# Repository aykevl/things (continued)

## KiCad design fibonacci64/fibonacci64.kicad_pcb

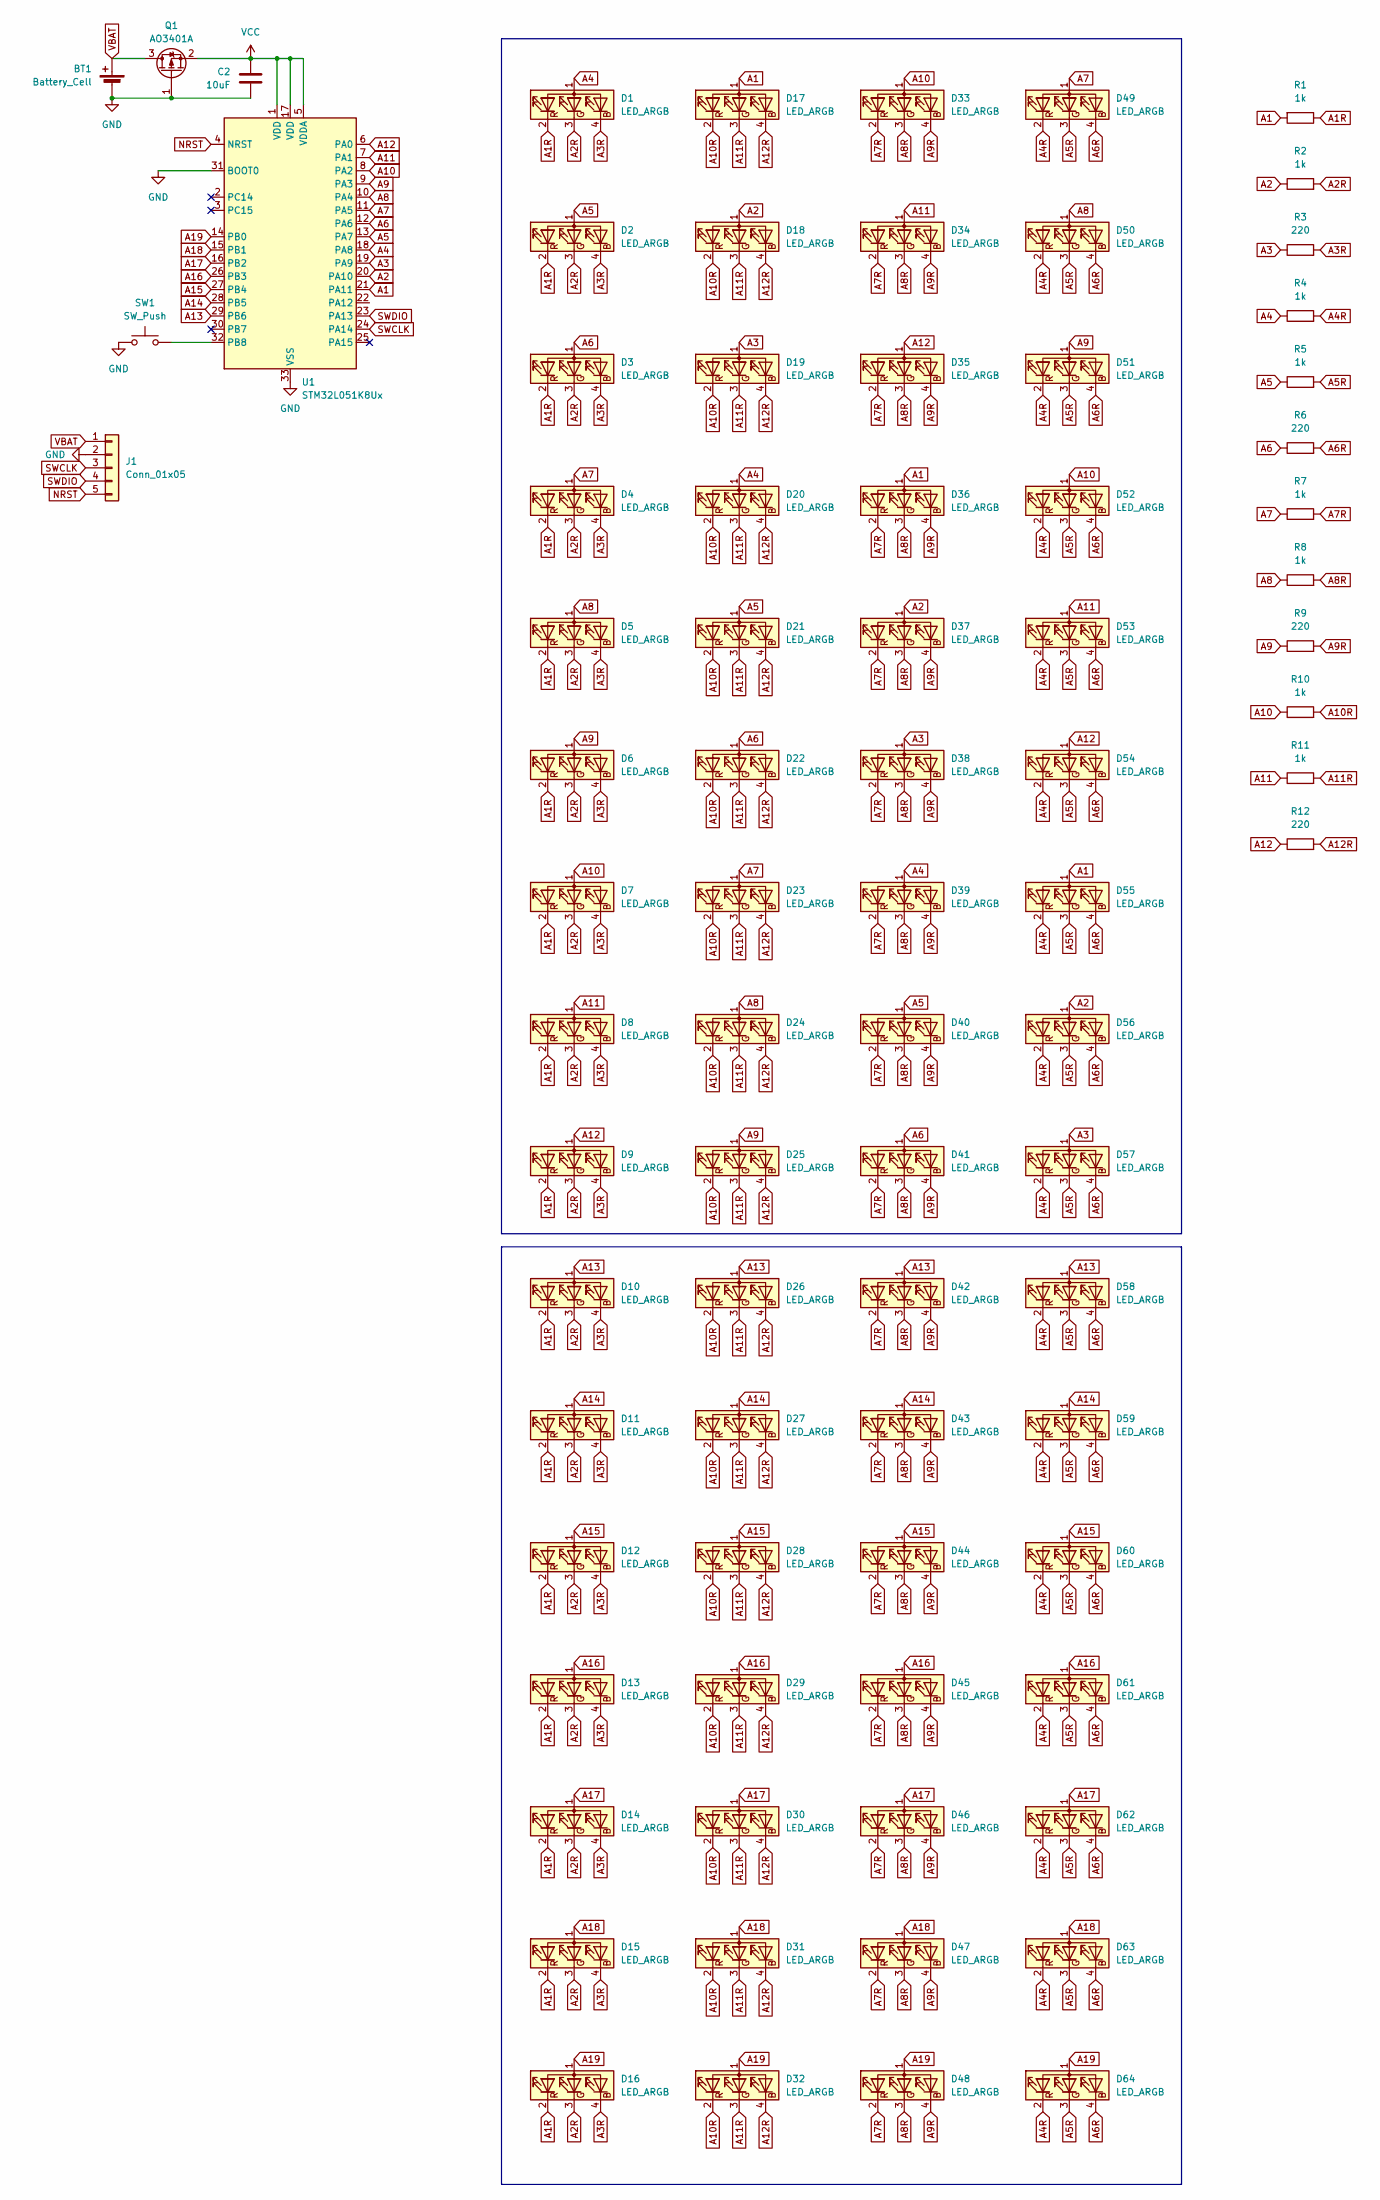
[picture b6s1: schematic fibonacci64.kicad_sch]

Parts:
BT1: Battery_Cell; BatteryHolder_Keystone_1060_1x2032; LCSC C964818
C2: 10uF; C_0402_1005Metric; LCSC C15525
D1, D2, D3, D4, D5, D6, D7, D8, D9, D10, D11, D12, D13, D14, D15, D16, D17, D18, D19, D20, D21, D22, D23, D24, D25, D26, D27, D28, D29, D30, D31, D32, D33, D34, D35, D36, D37, D38, D39, D40, D41, D42, D43, D44, D45, D46, D47, D48, D49, D50, D51, D52, D53, D54, D55, D56, D57, D58, D59, D60, D61, D62, D63, D64: LED_ARGB; NH-Z1415RGBA-SG; LCSC C2874117
J1: Conn_01x05; ProgramHeader
Q1: AO3401A; SOT-23; LCSC C15127
R1, R2, R4, R5, R7, R8, R10, R11: 1k; R_0402_1005Metric; LCSC C11702
R3, R6, R9, R12: 220; R_0402_1005Metric; LCSC C25091
SW1: SW_Push; SW_Push_SPST_NO_Alps_SKRK; LCSC C720477
U1: STM32L051K8Ux; QFN-32-1EP_5x5mm_P0.5mm_EP3.45x3.45mm; LCSC C94770

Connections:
A1: D17.1 (A), D36.1 (A), D55.1 (A), R1.2, U1.21 (PA11)
A1R: D1.2 (RK), D2.2 (RK), D3.2 (RK), D4.2 (RK), D5.2 (RK), D6.2 (RK), D7.2 (RK), D8.2 (RK), D9.2 (RK), D10.2 (RK), D11.2 (RK), D12.2 (RK), D13.2 (RK), D14.2 (RK), D15.2 (RK), D16.2 (RK), R1.1
A2: D18.1 (A), D37.1 (A), D56.1 (A), R2.1, U1.20 (PA10)
A2R: D1.3 (GK), D2.3 (GK), D3.3 (GK), D4.3 (GK), D5.3 (GK), D6.3 (GK), D7.3 (GK), D8.3 (GK), D9.3 (GK), D10.3 (GK), D11.3 (GK), D12.3 (GK), D13.3 (GK), D14.3 (GK), D15.3 (GK), D16.3 (GK), R2.2
A3: D19.1 (A), D38.1 (A), D57.1 (A), R3.1, U1.19 (PA9)
A3R: D1.4 (BK), D2.4 (BK), D3.4 (BK), D4.4 (BK), D5.4 (BK), D6.4 (BK), D7.4 (BK), D8.4 (BK), D9.4 (BK), D10.4 (BK), D11.4 (BK), D12.4 (BK), D13.4 (BK), D14.4 (BK), D15.4 (BK), D16.4 (BK), R3.2
A4: D1.1 (A), D20.1 (A), D39.1 (A), R4.1, U1.18 (PA8)
A4R: D49.2 (RK), D50.2 (RK), D51.2 (RK), D52.2 (RK), D53.2 (RK), D54.2 (RK), D55.2 (RK), D56.2 (RK), D57.2 (RK), D58.2 (RK), D59.2 (RK), D60.2 (RK), D61.2 (RK), D62.2 (RK), D63.2 (RK), D64.2 (RK), R4.2
A5: D2.1 (A), D21.1 (A), D40.1 (A), R5.1, U1.13 (PA7)
A5R: D49.3 (GK), D50.3 (GK), D51.3 (GK), D52.3 (GK), D53.3 (GK), D54.3 (GK), D55.3 (GK), D56.3 (GK), D57.3 (GK), D58.3 (GK), D59.3 (GK), D60.3 (GK), D61.3 (GK), D62.3 (GK), D63.3 (GK), D64.3 (GK), R5.2
A6: D3.1 (A), D22.1 (A), D41.1 (A), R6.1, U1.12 (PA6)
A6R: D49.4 (BK), D50.4 (BK), D51.4 (BK), D52.4 (BK), D53.4 (BK), D54.4 (BK), D55.4 (BK), D56.4 (BK), D57.4 (BK), D58.4 (BK), D59.4 (BK), D60.4 (BK), D61.4 (BK), D62.4 (BK), D63.4 (BK), D64.4 (BK), R6.2
A7: D4.1 (A), D23.1 (A), D49.1 (A), R7.1, U1.11 (PA5)
A7R: D33.2 (RK), D34.2 (RK), D35.2 (RK), D36.2 (RK), D37.2 (RK), D38.2 (RK), D39.2 (RK), D40.2 (RK), D41.2 (RK), D42.2 (RK), D43.2 (RK), D44.2 (RK), D45.2 (RK), D46.2 (RK), D47.2 (RK), D48.2 (RK), R7.2
A8: D5.1 (A), D24.1 (A), D50.1 (A), R8.1, U1.10 (PA4)
A8R: D33.3 (GK), D34.3 (GK), D35.3 (GK), D36.3 (GK), D37.3 (GK), D38.3 (GK), D39.3 (GK), D40.3 (GK), D41.3 (GK), D42.3 (GK), D43.3 (GK), D44.3 (GK), D45.3 (GK), D46.3 (GK), D47.3 (GK), D48.3 (GK), R8.2
A9: D6.1 (A), D25.1 (A), D51.1 (A), R9.1, U1.9 (PA3)
A9R: D33.4 (BK), D34.4 (BK), D35.4 (BK), D36.4 (BK), D37.4 (BK), D38.4 (BK), D39.4 (BK), D40.4 (BK), D41.4 (BK), D42.4 (BK), D43.4 (BK), D44.4 (BK), D45.4 (BK), D46.4 (BK), D47.4 (BK), D48.4 (BK), R9.2
A10: D7.1 (A), D33.1 (A), D52.1 (A), R10.1, U1.8 (PA2)
A10R: D17.2 (RK), D18.2 (RK), D19.2 (RK), D20.2 (RK), D21.2 (RK), D22.2 (RK), D23.2 (RK), D24.2 (RK), D25.2 (RK), D26.2 (RK), D27.2 (RK), D28.2 (RK), D29.2 (RK), D30.2 (RK), D31.2 (RK), D32.2 (RK), R10.2
A11: D8.1 (A), D34.1 (A), D53.1 (A), R11.1, U1.7 (PA1)
A11R: D17.3 (GK), D18.3 (GK), D19.3 (GK), D20.3 (GK), D21.3 (GK), D22.3 (GK), D23.3 (GK), D24.3 (GK), D25.3 (GK), D26.3 (GK), D27.3 (GK), D28.3 (GK), D29.3 (GK), D30.3 (GK), D31.3 (GK), D32.3 (GK), R11.2
A12: D9.1 (A), D35.1 (A), D54.1 (A), R12.1, U1.6 (PA0)
A12R: D17.4 (BK), D18.4 (BK), D19.4 (BK), D20.4 (BK), D21.4 (BK), D22.4 (BK), D23.4 (BK), D24.4 (BK), D25.4 (BK), D26.4 (BK), D27.4 (BK), D28.4 (BK), D29.4 (BK), D30.4 (BK), D31.4 (BK), D32.4 (BK), R12.2
A13: D10.1 (A), D26.1 (A), D42.1 (A), D58.1 (A), U1.29 (PB6)
A14: D11.1 (A), D27.1 (A), D43.1 (A), D59.1 (A), U1.28 (PB5)
A15: D12.1 (A), D28.1 (A), D44.1 (A), D60.1 (A), U1.27 (PB4)
A16: D13.1 (A), D29.1 (A), D45.1 (A), D61.1 (A), U1.26 (PB3)
A17: D14.1 (A), D30.1 (A), D46.1 (A), D62.1 (A), U1.16 (PB2)
A18: D15.1 (A), D31.1 (A), D47.1 (A), D63.1 (A), U1.15 (PB1)
A19: D16.1 (A), D32.1 (A), D48.1 (A), D64.1 (A), U1.14 (PB0)
GND: BT1.2 (-), C2.2, J1.2, Q1.1 (G), SW1.2, U1.31 (BOOT0), U1.33 (VSS)
NRST: J1.5, U1.4 (NRST)
unnamed: SW1.1, U1.32 (PB8)
SWCLK: J1.3, U1.24 (PA14)
SWDIO: J1.4, U1.23 (PA13)
VBAT: BT1.1 (+), J1.1, Q1.3 (D)
VCC: C2.1, Q1.2 (S), U1.1 (VDD), U1.5 (VDDA), U1.17 (VDD)

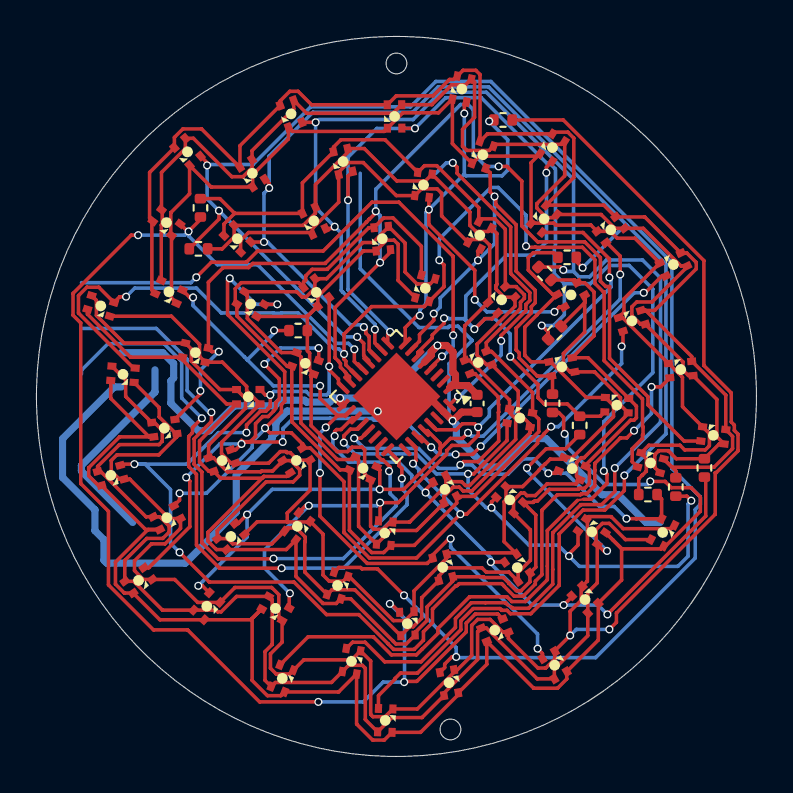
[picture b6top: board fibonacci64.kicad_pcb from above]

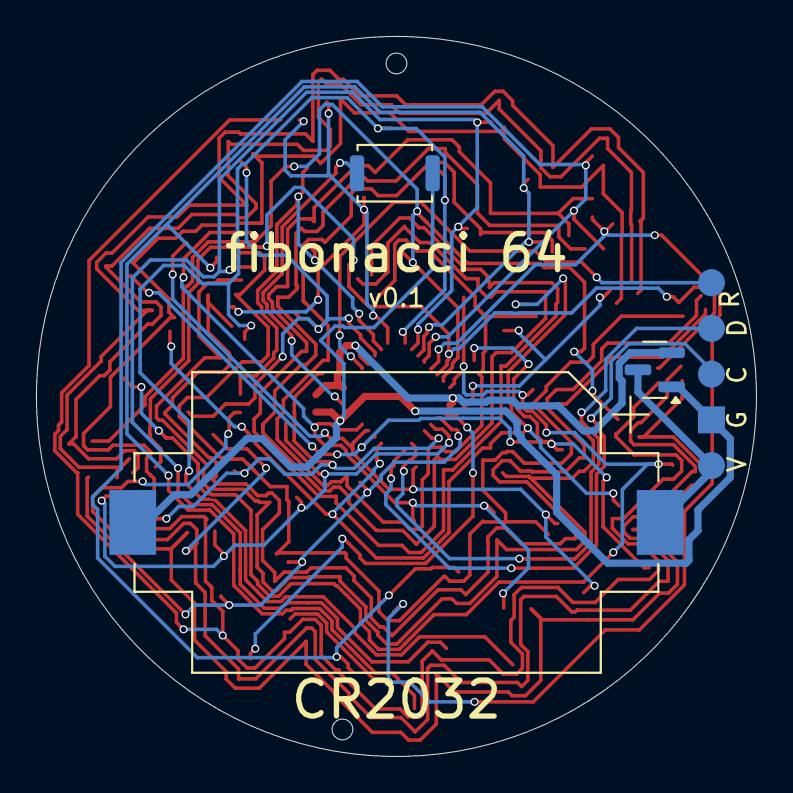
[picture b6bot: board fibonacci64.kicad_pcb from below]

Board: 2 copper layers, 40.0 x 40.0 mm, 82 parts (4 on the bottom side), 38 nets.

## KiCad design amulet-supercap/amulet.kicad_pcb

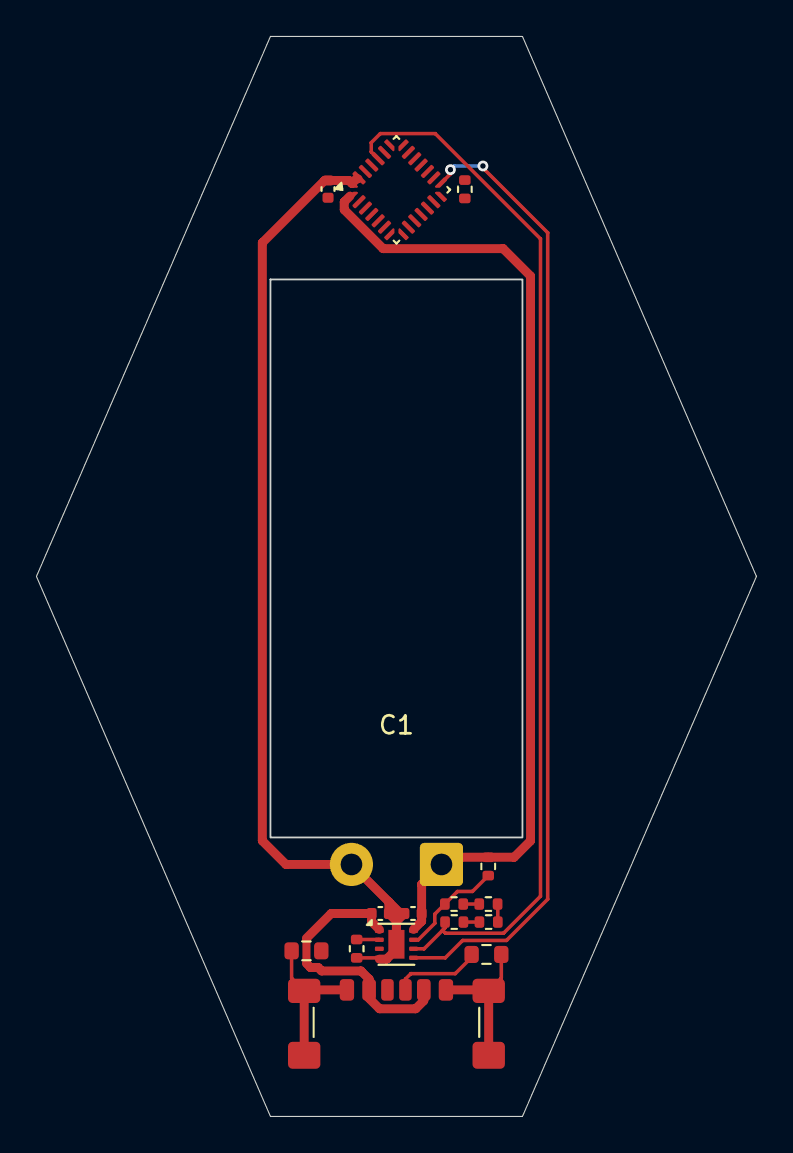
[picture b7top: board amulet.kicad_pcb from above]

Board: 2 copper layers, 40.0 x 60.0 mm, 17 parts (1 on the bottom side), 14 nets.

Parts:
C1: 350F; CP_Radial_D13.0mm_P7.50mm_350F
C2: 10uF; C_0402_1005Metric
C3, C4: 4.7uF; C_0402_1005Metric
J2: USB_C_Receptacle_PowerOnly_6P; USB_C_Receptacle_GCT_USB4135-GF-A_6P_TopMnt_Horizontal
R1, R2: 5.1k; R_0603_1608Metric
R3: 375; R_0402_1005Metric
R4, R5, R6, R7, R8: 200; R_0402_1005Metric
R9: 10k; R_0402_1005Metric
SW1: SW_Push; SW_Push_SPST_NO_Alps_SKRK
U1: BQ25173DSG; WSON-8-1EP_2x2mm_P0.5mm_EP0.9x1.6mm
U2: STM32L031G6Ux; QFN-28_4x4mm_P0.5mm

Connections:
FB: R4.2, R5.1, U1.7 (~FB)
GND: C1.2, C2.2, C3.2, C4.2, J2.A12 (GND), J2.B12 (GND), J2.S1 (SHIELD), R1.1, R2.1, R3.2, SW1.1, U1.4 (GND), U1.9 (GND), U2.16 (VSS), U2.27 (BOOT0), U2.28 (VSS)
ISET: R3.1, U1.2 (ISET)
NRST: U2.4 (NRST), U2.25 (PB6)
unnamed: J2.A5 (CC1), R1.2
unnamed: J2.B5 (CC2), R2.2
unnamed: R5.2, R6.1
unnamed: R6.2, R7.1
unnamed: R7.2, R8.1
unnamed: SW1.2, U2.26 (PB7)
PG: R8.2, U1.6 (~PG), U2.24 (PB3)
STAT: R9.1, U1.5 (STAT), U2.15 (PB1)
VBUS: C3.1, J2.A9 (VBUS), J2.B9 (VBUS), U1.1 (IN)
VCC: C1.1, C2.1, C4.1, R4.1, R9.2, U1.8 (OUT), U2.1 (VDD), U2.5 (VDDA), U2.17 (VDD)

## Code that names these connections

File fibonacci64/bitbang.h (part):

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        // 1 cycle bitplane
        "lsls %[tmp], #4\n\t"             // gap at the start
        "lsrs %[led0], #4\n\t"
        "adcs %[tmp], %[tmp], %[tmp]\n\t" // LED0 red   (A1/PA11)
        "rors %[led0], %[N8]\n\t"
        "adcs %[tmp], %[tmp], %[tmp]\n\t" // LED0 green (A2/PA10)
        "rors %[led0], %[N8]\n\t"
        "adcs %[tmp], %[tmp], %[tmp]\n\t" // LED0 blue  (A3/PA9)
        "lsls %[tmp], #3\n\t"             // gap between PA9 and PA5
        "lsrs %[led2], #4\n\t"
        "adcs %[tmp], %[tmp], %[tmp]\n\t" // LED2 red   (A7/PA5)
        "rors %[led2], %[N8]\n\t"
        "adcs %[tmp], %[tmp], %[tmp]\n\t" // LED2 green (A8/PA4)
        "rors %[led2], %[N8]\n\t"
        "adcs %[tmp], %[tmp], %[tmp]\n\t" // LED2 blue  (A9/PA3)
        "lsrs %[led1], #4\n\t"
        "adcs %[tmp], %[tmp], %[tmp]\n\t" // LED1 red   (A10/PA2)
        "rors %[led1], %[N8]\n\t"
        "adcs %[tmp], %[tmp], %[tmp]\n\t" // LED1 green (A11/PA1)
        "rors %[led1], %[N8]\n\t"
        "adcs %[tmp], %[tmp], %[tmp]\n\t" // LED1 blue  (A12/PA0)
        "eors %[tmp], %[xor]\n\t"

        // 2 cycle bitplane
        "lsls %[tmp], #4\n\t"             // gap at the start
        "rors %[led0], %[N8]\n\t"
        "lsrs %[led0], #9\n\t"
        "adcs %[tmp], %[tmp], %[tmp]\n\t" // LED0 red   (A1/PA11)
        "rors %[led0], %[N8]\n\t"
        "adcs %[tmp], %[tmp], %[tmp]\n\t" // LED0 green (A2/PA10)
        "rors %[led0], %[N8]\n\t"
        "adcs %[tmp], %[tmp], %[tmp]\n\t" // LED0 blue  (A3/PA9)
        "lsls %[tmp], #3\n\t"             // gap between PA9 and PA5
        "rors %[led2], %[N8]\n\t"
        "lsrs %[led2], #9\n\t"
        "adcs %[tmp], %[tmp], %[tmp]\n\t" // LED2 red   (A7/PA5)
        "rors %[led2], %[N8]\n\t"
        "adcs %[tmp], %[tmp], %[tmp]\n\t" // LED2 green (A8/PA4)
        "rors %[led2], %[N8]\n\t"
        "adcs %[tmp], %[tmp], %[tmp]\n\t" // LED2 blue  (A9/PA3)
        "rors %[led1], %[N8]\n\t"
        "lsrs %[led1], #9\n\t"
        "adcs %[tmp], %[tmp], %[tmp]\n\t" // LED1 red   (A10/PA2)
        "rors %[led1], %[N8]\n\t"
        "adcs %[tmp], %[tmp], %[tmp]\n\t" // LED1 green (A11/PA1)
        "rors %[led1], %[N8]\n\t"
        "adcs %[tmp], %[tmp], %[tmp]\n\t" // LED1 blue  (A12/PA0)
        "eors %[tmp], %[xor]\n\t"

        // Store 1-cycle and 2-cycle bitplanes.
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        "lsls %[tmp], #4\n\t"             // gap at the start
        "rors %[led0], %[N8]\n\t"
        "lsrs %[led0], #9\n\t"
        "adcs %[tmp], %[tmp], %[tmp]\n\t" // LED0 red   (A1/PA11)
        "rors %[led0], %[N8]\n\t"
        "adcs %[tmp], %[tmp], %[tmp]\n\t" // LED0 green (A2/PA10)
        "rors %[led0], %[N8]\n\t"
        "adcs %[tmp], %[tmp], %[tmp]\n\t" // LED0 blue  (A3/PA9)
        "lsls %[tmp], #3\n\t"             // gap between PA9 and PA5
        "rors %[led2], %[N8]\n\t"
        "lsrs %[led2], #9\n\t"
        "adcs %[tmp], %[tmp], %[tmp]\n\t" // LED2 red   (A7/PA5)
        "rors %[led2], %[N8]\n\t"
        "adcs %[tmp], %[tmp], %[tmp]\n\t" // LED2 green (A8/PA4)
        "rors %[led2], %[N8]\n\t"
        "adcs %[tmp], %[tmp], %[tmp]\n\t" // LED2 blue  (A9/PA3)
        "rors %[led1], %[N8]\n\t"
        "lsrs %[led1], #9\n\t"
        "adcs %[tmp], %[tmp], %[tmp]\n\t" // LED1 red   (A10/PA2)
        "rors %[led1], %[N8]\n\t"
        "adcs %[tmp], %[tmp], %[tmp]\n\t" // LED1 green (A11/PA1)
        "rors %[led1], %[N8]\n\t"
        "adcs %[tmp], %[tmp], %[tmp]\n\t" // LED1 blue  (A12/PA0)
        "eors %[tmp], %[xor]\n\t"

        // 8 cycle bitplane
        "lsls %[tmp], #4\n\t"             // gap at the start
        "rors %[led0], %[N8]\n\t"
        "lsrs %[led0], #9\n\t"
        "adcs %[tmp], %[tmp], %[tmp]\n\t" // LED0 red   (A1/PA11)
        "rors %[led0], %[N8]\n\t"
        "adcs %[tmp], %[tmp], %[tmp]\n\t" // LED0 green (A2/PA10)
        "rors %[led0], %[N8]\n\t"
        "adcs %[tmp], %[tmp], %[tmp]\n\t" // LED0 blue  (A3/PA9)
        "lsls %[tmp], #3\n\t"             // gap between PA9 and PA5
        "rors %[led2], %[N8]\n\t"
        "lsrs %[led2], #9\n\t"
        "adcs %[tmp], %[tmp], %[tmp]\n\t" // LED2 red   (A7/PA5)
        "rors %[led2], %[N8]\n\t"
        "adcs %[tmp], %[tmp], %[tmp]\n\t" // LED2 green (A8/PA4)
        "rors %[led2], %[N8]\n\t"
        "adcs %[tmp], %[tmp], %[tmp]\n\t" // LED2 blue  (A9/PA3)
        "rors %[led1], %[N8]\n\t"
        "lsrs %[led1], #9\n\t"
        "adcs %[tmp], %[tmp], %[tmp]\n\t" // LED1 red   (A10/PA2)
        "rors %[led1], %[N8]\n\t"
        "adcs %[tmp], %[tmp], %[tmp]\n\t" // LED1 green (A11/PA1)
        "rors %[led1], %[N8]\n\t"
        "adcs %[tmp], %[tmp], %[tmp]\n\t" // LED1 blue  (A12/PA0)
        "eors %[tmp], %[xor]\n\t"

        // Store 4-cycle and 8-cycle bitplanes.
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        "lsls %[tmp], #4\n\t"             // gap at the start
        "rors %[led0], %[N8]\n\t"
        "lsrs %[led0], #9\n\t"
        "adcs %[tmp], %[tmp], %[tmp]\n\t" // LED0 red   (A1/PA11)
        "rors %[led0], %[N8]\n\t"
        "adcs %[tmp], %[tmp], %[tmp]\n\t" // LED0 green (A2/PA10)
        "rors %[led0], %[N8]\n\t"
        "adcs %[tmp], %[tmp], %[tmp]\n\t" // LED0 blue  (A3/PA9)
        "lsls %[tmp], #3\n\t"             // gap between PA9 and PA5
        "rors %[led2], %[N8]\n\t"
        "lsrs %[led2], #9\n\t"
        "adcs %[tmp], %[tmp], %[tmp]\n\t" // LED2 red   (A7/PA5)
        "rors %[led2], %[N8]\n\t"
        "adcs %[tmp], %[tmp], %[tmp]\n\t" // LED2 green (A8/PA4)
        "rors %[led2], %[N8]\n\t"
        "adcs %[tmp], %[tmp], %[tmp]\n\t" // LED2 blue  (A9/PA3)
        "rors %[led1], %[N8]\n\t"
        "lsrs %[led1], #9\n\t"
        "adcs %[tmp], %[tmp], %[tmp]\n\t" // LED1 red   (A10/PA2)
        "rors %[led1], %[N8]\n\t"
        "adcs %[tmp], %[tmp], %[tmp]\n\t" // LED1 green (A11/PA1)
        "rors %[led1], %[N8]\n\t"
        "adcs %[tmp], %[tmp], %[tmp]\n\t" // LED1 blue  (A12/PA0)
        "eors %[tmp], %[xor]\n\t"

        // Store 16-cycle bitplane (of which the upper bits weren't cleared).
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        // 1 cycle bitplane
        "lsls %[tmp], #4\n\t"             // gap at the start
        "lsrs %[led0], #4\n\t"
        "adcs %[tmp], %[tmp], %[tmp]\n\t" // LED0 red   (A1/PA11)
        "rors %[led0], %[N8]\n\t"
        "adcs %[tmp], %[tmp], %[tmp]\n\t" // LED0 green (A2/PA10)
        "rors %[led0], %[N8]\n\t"
        "adcs %[tmp], %[tmp], %[tmp]\n\t" // LED0 blue  (A3/PA9)
        "lsrs %[led2], #4\n\t"
        "adcs %[tmp], %[tmp], %[tmp]\n\t" // LED2 red   (A4/PA8)
        "rors %[led2], %[N8]\n\t"
        "adcs %[tmp], %[tmp], %[tmp]\n\t" // LED2 green (A5/PA7)
        "rors %[led2], %[N8]\n\t"
        "adcs %[tmp], %[tmp], %[tmp]\n\t" // LED2 blue  (A6/PA6)
        "lsls %[tmp], #3\n\t"             // gap between PA6 and PA2
        "lsrs %[led1], #4\n\t"
        "adcs %[tmp], %[tmp], %[tmp]\n\t" // LED1 red   (A10/PA2)
        "rors %[led1], %[N8]\n\t"
        "adcs %[tmp], %[tmp], %[tmp]\n\t" // LED1 green (A11/PA1)
        "rors %[led1], %[N8]\n\t"
        "adcs %[tmp], %[tmp], %[tmp]\n\t" // LED1 blue  (A12/PA0)
        "eors %[tmp], %[xor]\n\t"

        // 2 cycle bitplane
        "lsls %[tmp], #4\n\t"             // gap at the start
        "rors %[led0], %[N8]\n\t"
        "lsrs %[led0], #9\n\t"
        "adcs %[tmp], %[tmp], %[tmp]\n\t" // LED0 red   (A1/PA11)
        "rors %[led0], %[N8]\n\t"
        "adcs %[tmp], %[tmp], %[tmp]\n\t" // LED0 green (A2/PA10)
        "rors %[led0], %[N8]\n\t"
        "adcs %[tmp], %[tmp], %[tmp]\n\t" // LED0 blue  (A3/PA9)
        "rors %[led2], %[N8]\n\t"
        "lsrs %[led2], #9\n\t"
        "adcs %[tmp], %[tmp], %[tmp]\n\t" // LED2 red   (A4/PA8)
        "rors %[led2], %[N8]\n\t"
        "adcs %[tmp], %[tmp], %[tmp]\n\t" // LED2 green (A5/PA7)
        "rors %[led2], %[N8]\n\t"
        "adcs %[tmp], %[tmp], %[tmp]\n\t" // LED2 blue  (A6/PA6)
        "lsls %[tmp], #3\n\t"             // gap between PA6 and PA2
        "rors %[led1], %[N8]\n\t"
        "lsrs %[led1], #9\n\t"
        "adcs %[tmp], %[tmp], %[tmp]\n\t" // LED1 red   (A10/PA2)
        "rors %[led1], %[N8]\n\t"
        "adcs %[tmp], %[tmp], %[tmp]\n\t" // LED1 green (A11/PA1)
        "rors %[led1], %[N8]\n\t"
        "adcs %[tmp], %[tmp], %[tmp]\n\t" // LED1 blue  (A12/PA0)
        "eors %[tmp], %[xor]\n\t"

        // Store 1-cycle and 2-cycle bitplanes.
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        "lsls %[tmp], #4\n\t"             // gap at the start
        "rors %[led0], %[N8]\n\t"
        "lsrs %[led0], #9\n\t"
        "adcs %[tmp], %[tmp], %[tmp]\n\t" // LED0 red   (A1/PA11)
        "rors %[led0], %[N8]\n\t"
        "adcs %[tmp], %[tmp], %[tmp]\n\t" // LED0 green (A2/PA10)
        "rors %[led0], %[N8]\n\t"
        "adcs %[tmp], %[tmp], %[tmp]\n\t" // LED0 blue  (A3/PA9)
        "rors %[led2], %[N8]\n\t"
        "lsrs %[led2], #9\n\t"
        "adcs %[tmp], %[tmp], %[tmp]\n\t" // LED2 red   (A4/PA8)
        "rors %[led2], %[N8]\n\t"
        "adcs %[tmp], %[tmp], %[tmp]\n\t" // LED2 green (A5/PA7)
        "rors %[led2], %[N8]\n\t"
        "adcs %[tmp], %[tmp], %[tmp]\n\t" // LED2 blue  (A6/PA6)
        "lsls %[tmp], #3\n\t"             // gap between PA6 and PA2
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
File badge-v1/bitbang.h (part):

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
        // 1 and 2 cycle bitplane
        "lsls %[tmp], #14\n\t"            // gap at the beginning
        "lsrs %[led0], #3\n\t"            // LED0 red   (A4/PB8)
        "adcs %[tmp], %[tmp], %[tmp]\n\t"
        "lsrs %[led0], #1\n\t"
        "adcs %[tmp], %[tmp], %[tmp]\n\t"
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        "adcs %[tmp], %[tmp], %[tmp]\n\t"
        "lsrs %[led0], #1\n\t"
        "adcs %[tmp], %[tmp], %[tmp]\n\t"
        "rors %[led0], %[N7]\n\t"         // LED0 blue  (A6/PB6)
        "adcs %[tmp], %[tmp], %[tmp]\n\t"
        "lsrs %[led0], #1\n\t"
        "adcs %[tmp], %[tmp], %[tmp]\n\t"
        "lsrs %[led1], #3\n\t"            // LED1 red   (A7/PB5)
        "adcs %[tmp], %[tmp], %[tmp]\n\t"
        "lsrs %[led1], #1\n\t"
        "adcs %[tmp], %[tmp], %[tmp]\n\t"
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        "adcs %[tmp], %[tmp], %[tmp]\n\t"
        "lsrs %[led1], #1\n\t"
        "adcs %[tmp], %[tmp], %[tmp]\n\t"
        "rors %[led1], %[N7]\n\t"         // LED1 blue  (A9/PB3)
        "adcs %[tmp], %[tmp], %[tmp]\n\t"
        "lsrs %[led1], #1\n\t"
        "adcs %[tmp], %[tmp], %[tmp]\n\t"
        "lsrs %[led2], #3\n\t"            // LED2 red   (A10/PB2)
        "adcs %[tmp], %[tmp], %[tmp]\n\t"
        "lsrs %[led2], #1\n\t"
        "adcs %[tmp], %[tmp], %[tmp]\n\t"
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        "adcs %[tmp], %[tmp], %[tmp]\n\t"
        "lsrs %[led2], #1\n\t"
        "adcs %[tmp], %[tmp], %[tmp]\n\t"
        "rors %[led2], %[N7]\n\t"         // LED2 blue  (A12/PB0)
        "adcs %[tmp], %[tmp], %[tmp]\n\t"
        "lsrs %[led2], #1\n\t"
        "adcs %[tmp], %[tmp], %[tmp]\n\t"
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        // 4 and 8 cycle bitplane
        "lsls %[tmp], #14\n\t"            // gap at the beginning
        "rors %[led0], %[N7]\n\t"
        "lsrs %[led0], #10\n\t"           // LED0 red   (A4/PB8)
        "adcs %[tmp], %[tmp], %[tmp]\n\t"
        "lsrs %[led0], #1\n\t"
        "adcs %[tmp], %[tmp], %[tmp]\n\t"
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        "adcs %[tmp], %[tmp], %[tmp]\n\t"
        "lsrs %[led0], #1\n\t"
        "adcs %[tmp], %[tmp], %[tmp]\n\t"
        "rors %[led0], %[N7]\n\t"         // LED0 blue  (A6/PB6)
        "adcs %[tmp], %[tmp], %[tmp]\n\t"
        "lsrs %[led0], #1\n\t"
        "adcs %[tmp], %[tmp], %[tmp]\n\t"
        "rors %[led1], %[N7]\n\t"
        "lsrs %[led1], #10\n\t"           // LED1 red   (A7/PB5)
        "adcs %[tmp], %[tmp], %[tmp]\n\t"
        "lsrs %[led1], #1\n\t"
        "adcs %[tmp], %[tmp], %[tmp]\n\t"
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        "adcs %[tmp], %[tmp], %[tmp]\n\t"
        "lsrs %[led1], #1\n\t"
        "adcs %[tmp], %[tmp], %[tmp]\n\t"
        "rors %[led1], %[N7]\n\t"         // LED1 blue  (A9/PB3)
        "adcs %[tmp], %[tmp], %[tmp]\n\t"
        "lsrs %[led1], #1\n\t"
        "adcs %[tmp], %[tmp], %[tmp]\n\t"
        "rors %[led2], %[N7]\n\t"
        "lsrs %[led2], #10\n\t"           // LED2 red   (A10/PB2)
        "adcs %[tmp], %[tmp], %[tmp]\n\t"
        "lsrs %[led2], #1\n\t"
        "adcs %[tmp], %[tmp], %[tmp]\n\t"
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        "adcs %[tmp], %[tmp], %[tmp]\n\t"
        "lsrs %[led2], #1\n\t"
        "adcs %[tmp], %[tmp], %[tmp]\n\t"
        "rors %[led2], %[N7]\n\t"         // LED2 blue  (A12/PB0)
        "adcs %[tmp], %[tmp], %[tmp]\n\t"
        "lsrs %[led2], #1\n\t"
        "adcs %[tmp], %[tmp], %[tmp]\n\t"
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        // 16 and 32 cycle bitplane
        "lsls %[tmp], #14\n\t"            // gap at the beginning
        "rors %[led0], %[N7]\n\t"
        "lsrs %[led0], #10\n\t"           // LED0 red   (A4/PB8)
        "adcs %[tmp], %[tmp], %[tmp]\n\t"
        "lsrs %[led0], #1\n\t"
        "adcs %[tmp], %[tmp], %[tmp]\n\t"
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        "adcs %[tmp], %[tmp], %[tmp]\n\t"
        "lsrs %[led0], #1\n\t"
        "adcs %[tmp], %[tmp], %[tmp]\n\t"
        "rors %[led0], %[N7]\n\t"         // LED0 blue  (A6/PB6)
        "adcs %[tmp], %[tmp], %[tmp]\n\t"
        "lsrs %[led0], #1\n\t"
        "adcs %[tmp], %[tmp], %[tmp]\n\t"
        "rors %[led1], %[N7]\n\t"
        "lsrs %[led1], #10\n\t"           // LED1 red   (A7/PB5)
        "adcs %[tmp], %[tmp], %[tmp]\n\t"
        "lsrs %[led1], #1\n\t"
        "adcs %[tmp], %[tmp], %[tmp]\n\t"
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        "adcs %[tmp], %[tmp], %[tmp]\n\t"
        "lsrs %[led1], #1\n\t"
        "adcs %[tmp], %[tmp], %[tmp]\n\t"
        "rors %[led1], %[N7]\n\t"         // LED1 blue  (A9/PB3)
        "adcs %[tmp], %[tmp], %[tmp]\n\t"
        "lsrs %[led1], #1\n\t"
        "adcs %[tmp], %[tmp], %[tmp]\n\t"
        "rors %[led2], %[N7]\n\t"
        "lsrs %[led2], #10\n\t"           // LED2 red   (A10/PB2)
        "adcs %[tmp], %[tmp], %[tmp]\n\t"
        "lsrs %[led2], #1\n\t"
        "adcs %[tmp], %[tmp], %[tmp]\n\t"
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        "adcs %[tmp], %[tmp], %[tmp]\n\t"
        "lsrs %[led2], #1\n\t"
        "adcs %[tmp], %[tmp], %[tmp]\n\t"
        "rors %[led2], %[N7]\n\t"         // LED2 blue  (A12/PB0)
        "adcs %[tmp], %[tmp], %[tmp]\n\t"
        "lsrs %[led2], #1\n\t"
        "adcs %[tmp], %[tmp], %[tmp]\n\t"
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
        // 1 and 2 cycle bitplane
        "lsls %[tmp], #8\n\t"             // gap at the beginning
        "lsrs %[led0], #3\n\t"            // LED0 red   (A1/PB11)
        "adcs %[tmp], %[tmp], %[tmp]\n\t"
        "lsrs %[led0], #1\n\t"
        "adcs %[tmp], %[tmp], %[tmp]\n\t"
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        "adcs %[tmp], %[tmp], %[tmp]\n\t"
        "lsrs %[led0], #1\n\t"
        "adcs %[tmp], %[tmp], %[tmp]\n\t"
        "rors %[led0], %[N7]\n\t"         // LED0 blue  (A3/PB9)
        "adcs %[tmp], %[tmp], %[tmp]\n\t"
        "lsrs %[led0], #1\n\t"
        "adcs %[tmp], %[tmp], %[tmp]\n\t"
        "lsrs %[led1], #3\n\t"            // LED1 red   (A4/PB8)
        "adcs %[tmp], %[tmp], %[tmp]\n\t"
        "lsrs %[led1], #1\n\t"
        "adcs %[tmp], %[tmp], %[tmp]\n\t"
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        "adcs %[tmp], %[tmp], %[tmp]\n\t"
        "lsrs %[led1], #1\n\t"
        "adcs %[tmp], %[tmp], %[tmp]\n\t"
        "rors %[led1], %[N7]\n\t"         // LED1 blue  (A6/PB6)
        "adcs %[tmp], %[tmp], %[tmp]\n\t"
        "lsrs %[led1], #1\n\t"
        "adcs %[tmp], %[tmp], %[tmp]\n\t"
        "lsrs %[led2], #3\n\t"            // LED2 red   (A7/PB6)
        "adcs %[tmp], %[tmp], %[tmp]\n\t"
        "lsrs %[led2], #1\n\t"
        "adcs %[tmp], %[tmp], %[tmp]\n\t"
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        "adcs %[tmp], %[tmp], %[tmp]\n\t"
        "lsrs %[led2], #1\n\t"
        "adcs %[tmp], %[tmp], %[tmp]\n\t"
        "rors %[led2], %[N7]\n\t"         // LED2 blue  (A9/PB3)
        "adcs %[tmp], %[tmp], %[tmp]\n\t"
        "lsrs %[led2], #1\n\t"
        "adcs %[tmp], %[tmp], %[tmp]\n\t"
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        // 4 and 8 cycle bitplane
        "lsls %[tmp], #8\n\t"             // gap at the beginning
        "rors %[led0], %[N7]\n\t"
        "lsrs %[led0], #10\n\t"           // LED0 red   (A1/PB11)
        "adcs %[tmp], %[tmp], %[tmp]\n\t"
        "lsrs %[led0], #1\n\t"
        "adcs %[tmp], %[tmp], %[tmp]\n\t"
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        "adcs %[tmp], %[tmp], %[tmp]\n\t"
        "lsrs %[led0], #1\n\t"
        "adcs %[tmp], %[tmp], %[tmp]\n\t"
        "rors %[led0], %[N7]\n\t"         // LED0 blue  (A3/PB9)
        "adcs %[tmp], %[tmp], %[tmp]\n\t"
        "lsrs %[led0], #1\n\t"
        "adcs %[tmp], %[tmp], %[tmp]\n\t"
        "rors %[led1], %[N7]\n\t"
        "lsrs %[led1], #10\n\t"           // LED1 red   (A4/PB8)
        "adcs %[tmp], %[tmp], %[tmp]\n\t"
        "lsrs %[led1], #1\n\t"
        "adcs %[tmp], %[tmp], %[tmp]\n\t"
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        "adcs %[tmp], %[tmp], %[tmp]\n\t"
        "lsrs %[led1], #1\n\t"
        "adcs %[tmp], %[tmp], %[tmp]\n\t"
        "rors %[led1], %[N7]\n\t"         // LED1 blue  (A6/PB6)
        "adcs %[tmp], %[tmp], %[tmp]\n\t"
        "lsrs %[led1], #1\n\t"
        "adcs %[tmp], %[tmp], %[tmp]\n\t"
        "rors %[led2], %[N7]\n\t"
        "lsrs %[led2], #10\n\t"           // LED2 red   (A7/PB6)
        "adcs %[tmp], %[tmp], %[tmp]\n\t"
        "lsrs %[led2], #1\n\t"
        "adcs %[tmp], %[tmp], %[tmp]\n\t"
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        "adcs %[tmp], %[tmp], %[tmp]\n\t"
        "lsrs %[led2], #1\n\t"
        "adcs %[tmp], %[tmp], %[tmp]\n\t"
        "rors %[led2], %[N7]\n\t"         // LED2 blue  (A9/PB3)
        "adcs %[tmp], %[tmp], %[tmp]\n\t"
        "lsrs %[led2], #1\n\t"
        "adcs %[tmp], %[tmp], %[tmp]\n\t"
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        // 16 and 32 cycle bitplane
        "lsls %[tmp], #8\n\t"             // gap at the beginning
        "rors %[led0], %[N7]\n\t"
        "lsrs %[led0], #10\n\t"           // LED0 red   (A1/PB11)
        "adcs %[tmp], %[tmp], %[tmp]\n\t"
        "lsrs %[led0], #1\n\t"
        "adcs %[tmp], %[tmp], %[tmp]\n\t"
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        "adcs %[tmp], %[tmp], %[tmp]\n\t"
        "lsrs %[led0], #1\n\t"
        "adcs %[tmp], %[tmp], %[tmp]\n\t"
        "rors %[led0], %[N7]\n\t"         // LED0 blue  (A3/PB9)
        "adcs %[tmp], %[tmp], %[tmp]\n\t"
        "lsrs %[led0], #1\n\t"
        "adcs %[tmp], %[tmp], %[tmp]\n\t"
        "rors %[led1], %[N7]\n\t"
        "lsrs %[led1], #10\n\t"           // LED1 red   (A4/PB8)
        "adcs %[tmp], %[tmp], %[tmp]\n\t"
        "lsrs %[led1], #1\n\t"
        "adcs %[tmp], %[tmp], %[tmp]\n\t"
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        "adcs %[tmp], %[tmp], %[tmp]\n\t"
        "lsrs %[led1], #1\n\t"
        "adcs %[tmp], %[tmp], %[tmp]\n\t"
        "rors %[led1], %[N7]\n\t"         // LED1 blue  (A6/PB6)
        "adcs %[tmp], %[tmp], %[tmp]\n\t"
        "lsrs %[led1], #1\n\t"
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
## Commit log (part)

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2018-11-17 Lots of new animations, including gyro
2019-04-26 spirit-level: add Ciruit Play Express thing to measure horizontal things
2019-09-18 hub75: add fire pattern to hub75 example
2019-12-28 hub75: add support for samd51
2020-01-25 hub75: use a config struct for easier changing of parameters
2020-01-25 hub75: add Brightness configuration option
2020-01-25 hub75: initialize bitstrings at start
    This shaves off another ~0.3ms for 6 screens.
2020-01-31 ledcube: add radiance demo
2020-07-06 poi: use proper bluetooth package version
    The previous version is incompatible.
2020-07-29 poi: update to new SPI naming convetions (SDO, SDI)
2020-08-09 poi: fix rotation speed calculation to avoid overflow
    Previously there was an integer overflow, this is fixed by reducing
    rotation speed to a .1° precision (down from .01° precision).
    This makes the noise animation actually work.
2020-09-13 poi: let animation speed depend on rotation speed
    Let the animation continue slowly when not moving while providing the
    same visual effect independent of the rotation speed.
2020-09-14 poi: show more sparkles
2021-06-28 poi: update drivers to fix issue with sk9822
2021-06-28 poi: lower advertising interval
    This saves some current, before this commit most current would go
    towards advertisement.
2022-04-15 poi: simplify Makefile
2022-04-15 poi: update ledsgo version
2022-07-25 mch2022-noise: speed up the code a little
2022-07-26 mch2022-noise: change SPI frequency from 40MHz to 80MHz
    This seems to actually work, even if it's probably way out of spec for
    the ILI9341 display.
2022-09-12 earring-leaf: make brightness vs frequency controllable
2022-09-12 earring-leaf: use an enum to define various modes
2022-10-17 cloud: add pico support
2023-02-07 cloud: add a few more noise patterns
2023-03-02 WIP README
2023-03-25 games: add "brick breaker" style game
    Code isn't very clean, just stashing this now so I don't lose it.
2023-03-31 brick-breaker: use board abstraction
    Use my experimental github.com/aykevl/board abstraction layer for TinyGo
    programs.
2023-04-08 Add simple badge
    The only thing that is implemented is a simple menu and a Mandelbrot
    renderer.
2023-04-10 board: add new touch input test
    Also fix refreshing the screen when returning from an app.
2023-04-11 WIP tearing test on the gopher badge
2023-04-13 badge: add tearing test
2023-04-15 watch: simulate slow SPI speed
    I've actually set it lower than it is in reality, to make the slowness
    more obvious during development.
2023-04-15 watch: fix simulator
2023-04-15 watch: turn off the screen when pressing the button on the homescreen
2023-04-18 watch: go back to homescreen after closing time settings
    Not checking the event resulted in two events happening at once.
2023-04-18 watch: add battery sensor support
2023-04-24 badge: add sensor details
    This only shows the battery, but more sensors may be added in the
    future (like an accelerometer).
2023-04-30 watch: add early BLE support
    This just advertises "GopherWatch" and doesn't do anything else. In the
    future, it should support updating the time among others.
2023-05-07 watch: update dependencies
    This pulls a fix that should fix the touch controller after InfiniTime
    has configured it.
2023-05-08 watch: support non-bluetooth boards
2023-05-09 watch: add screen rotate support
    The touch sensor isn't updated yet, this requires the fix here:
    https://github.com/tinygo-org/drivers/pull/568
2023-05-10 watch: don't use SetUpdateCallback
    Just run the input reader in the main loop whenever convenient.
    This reduces code size a little bit too, so that's great.
2023-05-10 watch: show the currently selected screen timeout value
2023-05-12 watch: make the apps/settings view scrollable
2023-05-19 earring-ring: reverse order in which bits are displayed
    This allows me to use the full 8-bit value for color data, and makes it
    easier to change the number of bits used for display.
2023-05-19 earring-ring: add colored tracer animation
2023-05-20 earring-ring: disable interrupts while updating the LEDs
    This might result in flickering otherwise.
2023-05-21 earring-ring: add support for the button
2023-05-22 watch: update board dependency
    Among others, this brings in RGB444 support which improves performance
    quite a bit.
2023-05-23 earring-ring: add fire and ice animation
2023-05-27 earring-ring: add sparkle animation
2023-06-26 badge: more closely simulate the Gopher Badge
    That's the one we'll usually use in practice.
2023-07-15 badge: update mandelbrot to tinygl package
    This is part of a refactor.
2023-08-08 earring-ring: add fire animation
2023-09-10 Add README file with a license
    Because a README is a good idea and it's also a good idea to say how the
    code can be used.
2023-11-02 badge: update due to API changes
2023-11-04 hub75: update IRQ handling for recent TinyGo versions
2023-11-21 watch: use hardware scrolling
2023-11-21 watch: fix watchface after adjusting time
    There was a bug where the watch would show the old time after adjusting
    only the hours (but not the minutes). This is fixed by also checking
    whether the hours have been updated.
2023-11-24 watch: update to new API
2023-12-18 watch: fix "test touch" tool
    It previously crashed.
2023-12-21 watch: add analog watch face
2023-12-24 watch: add Device Information Service
2024-01-05 watch: improve Bluetooth error handling
    Actually show an error when one occurs.
2024-01-05 watch: remove ability to set the time
    The time is now automatically updated via the phone, so there's no need
    to set it on the watch itself.
    This saves over 2kB in flash.
2024-01-06 watch: publish step count value over BLE
2024-01-06 watch: remove "touch test"
    This was useful as a test, but not really useful now. Removing it saves
    about 1kB of flash usage.
2024-01-31 badge: update tinygl dependency
    This fixes a rendering bug when using hardware scrolling on a display.
2024-02-03 brick-breaker: update board dependency
2024-02-03 watch: update simulator screenshot in the README
2024-09-12 goggles-8ring: add new goggles project
2025-01-13 hub75: ability to use SPI1 bus on SAMD51, such as the Metro-M4 board, as long as it is still on SERCOM1.
2025-02-08 earring-ring-rgb36: small changes
    * use a single capacitor instead of two (apparently that's just fine)
    * add a NRST test point
2025-02-10 earring-ring-rgb36: rotate net names so the labels make a bit more sense
2025-05-23 earring-ring-rgb36: added reset pin to programming pins on the side
2025-07-15 earring-ring-rgb36: implement sleep mode (~1µA)
    Also refactor a bit.
2025-07-15 earring-ring-rgb36: make bitbanging slightly more efficient
    Removes some rotate instructions (~10 cycles per update), and updates
    the bitbang assembly to load just one register at the start (~24 cycles
    per update).
2025-07-16 earring-ring-rgb36: add some test patterns
2025-07-24 glove-v1: new gloving LEDs (for flow arts)
    Not tested in production.
2025-08-11 earring-ring-rgb36: use long press to shutdown/poweron
2025-08-14 fibonacci64: update animations
2025-10-15 earring-ring-rgb36: use 6 bits color depth
2025-10-27 badge-v1: initial version
2025-11-09 ws2812-matrix: gnd not via bottom layer
2025-11-13 ws2812-matrix: switch to SK6805-EC14
    This LED is in stock at JLCPCB, unlike the SK6805-EC10.
2025-11-28 co2sensor: use SCD41 periodic measurements for lower power consumption
2025-12-09 earring-ring-rgb36: add README
2025-12-30 earring-ring-rgb36: add card that I printed
2026-01-14 earring-ring-rgb36v2: initial commit
2026-01-14 earring-ring-rgb36v2: add 32768Hz crystal oscillator
    No idea whether this is correct, might need some additional checking.
2026-01-14 earring-ring-rgb36v2: set thickness to 0.8mm
2026-01-14 earring-ring-rgb36v2: add 3D model for the microphone
    Also remove the tooling hole at the bottom, they were messing with the
    3D view.
2026-01-30 earring-ring-rgb36: add firmware that is on most earrings
    For reproducibility, let's commit the firmware itself.
2026-02-17 earring-ring-rgb36v2: many changes for next prototype
    * remove crystal
    * remove light sensor
    * add extra button
    * add capacitor to VDDA and to the microphone
    * move capacitor to above the chip
    * many small changes to make the design look a bit more symmetric
2026-03-16 earring-ring-rgb36v2: extend PCB panel to 3x4 PCBs
    This increases the boards per panel from 6 to 12, which makes handling a
    bit easier and allows for larger order sizes (with the prototyping
    service that is limited to 30 panels).
2026-03-19 earring-ring-rgb36v2: update to new prototype PCB
    Also make sure the microphone is still usable after it is turned on
    (don't keep it in reset).
2026-03-23 earring-ring-rgb36v2: change wiring slightly to be more sensible
    The button had some weird wiring, it makes much more sense to connect
    the button between a pin and ground.
2026-03-23 earring-ring-rgb36v3: mouse bytes at bottom tooling hole
2026-03-25 earring-ring-rgb36v2: add a bunch more noise patterns
2026-03-26 earring-ring-rgb36v3: prepare for ordering
    * Replace main MCU with a cheaper (in bulk) variant.
    (that is also in stock at JLCPCB)
    * Fix main MCU orientation (it's rotated differently at JLCPCB)
    * Replace red and green LED resistor with a higher value.
    Blue tends to be slightly dimmer, this might help with that.
2026-03-30 earring-ring-rgb36v2: add 3 more fire colors
2026-04-25 Add the pan flag to the 36led earings
2026-06-01 earring-ring-rgb36v2: refactor per-frame animation updates
2026-06-01 earring-ring-rgb36v2: make sparkles more sparkly
2026-06-01 earring-ring-rgb36v2: first mode is QA mode
    This is useful during mass flashing and testing.
2026-06-06 earring-ring-rgb36: add sparkle mode
2026-06-10 earring-ring-rgb36v2: add README
2026-06-21 earring-ring-rgb36v2: only call setup/nextFrame on valid pattern
    This avoids a crash when there is no valid pattern.
2026-06-21 earring-ring-rgb36v2: try to fix a HardFault
    Not sure what's going on here, but it might help.
    Also change default from 17 to 16 which is the actual default.
2026-06-22 earring-ring-rgb36v2: calibrate by adjusting timer, not HSI16 trim
    For some reason, adjusting HSI16TRIM will sometimes result in a hard
    fault. One out of 10 times or so. I don't know why.
    But we can adjust the trim value in a different way: by changing the
    prescaler of the clock source. And this seems to work just as well, and
    doesn't crash.
    Future improvements: adjust the ARR value instead of the PSC value, this
